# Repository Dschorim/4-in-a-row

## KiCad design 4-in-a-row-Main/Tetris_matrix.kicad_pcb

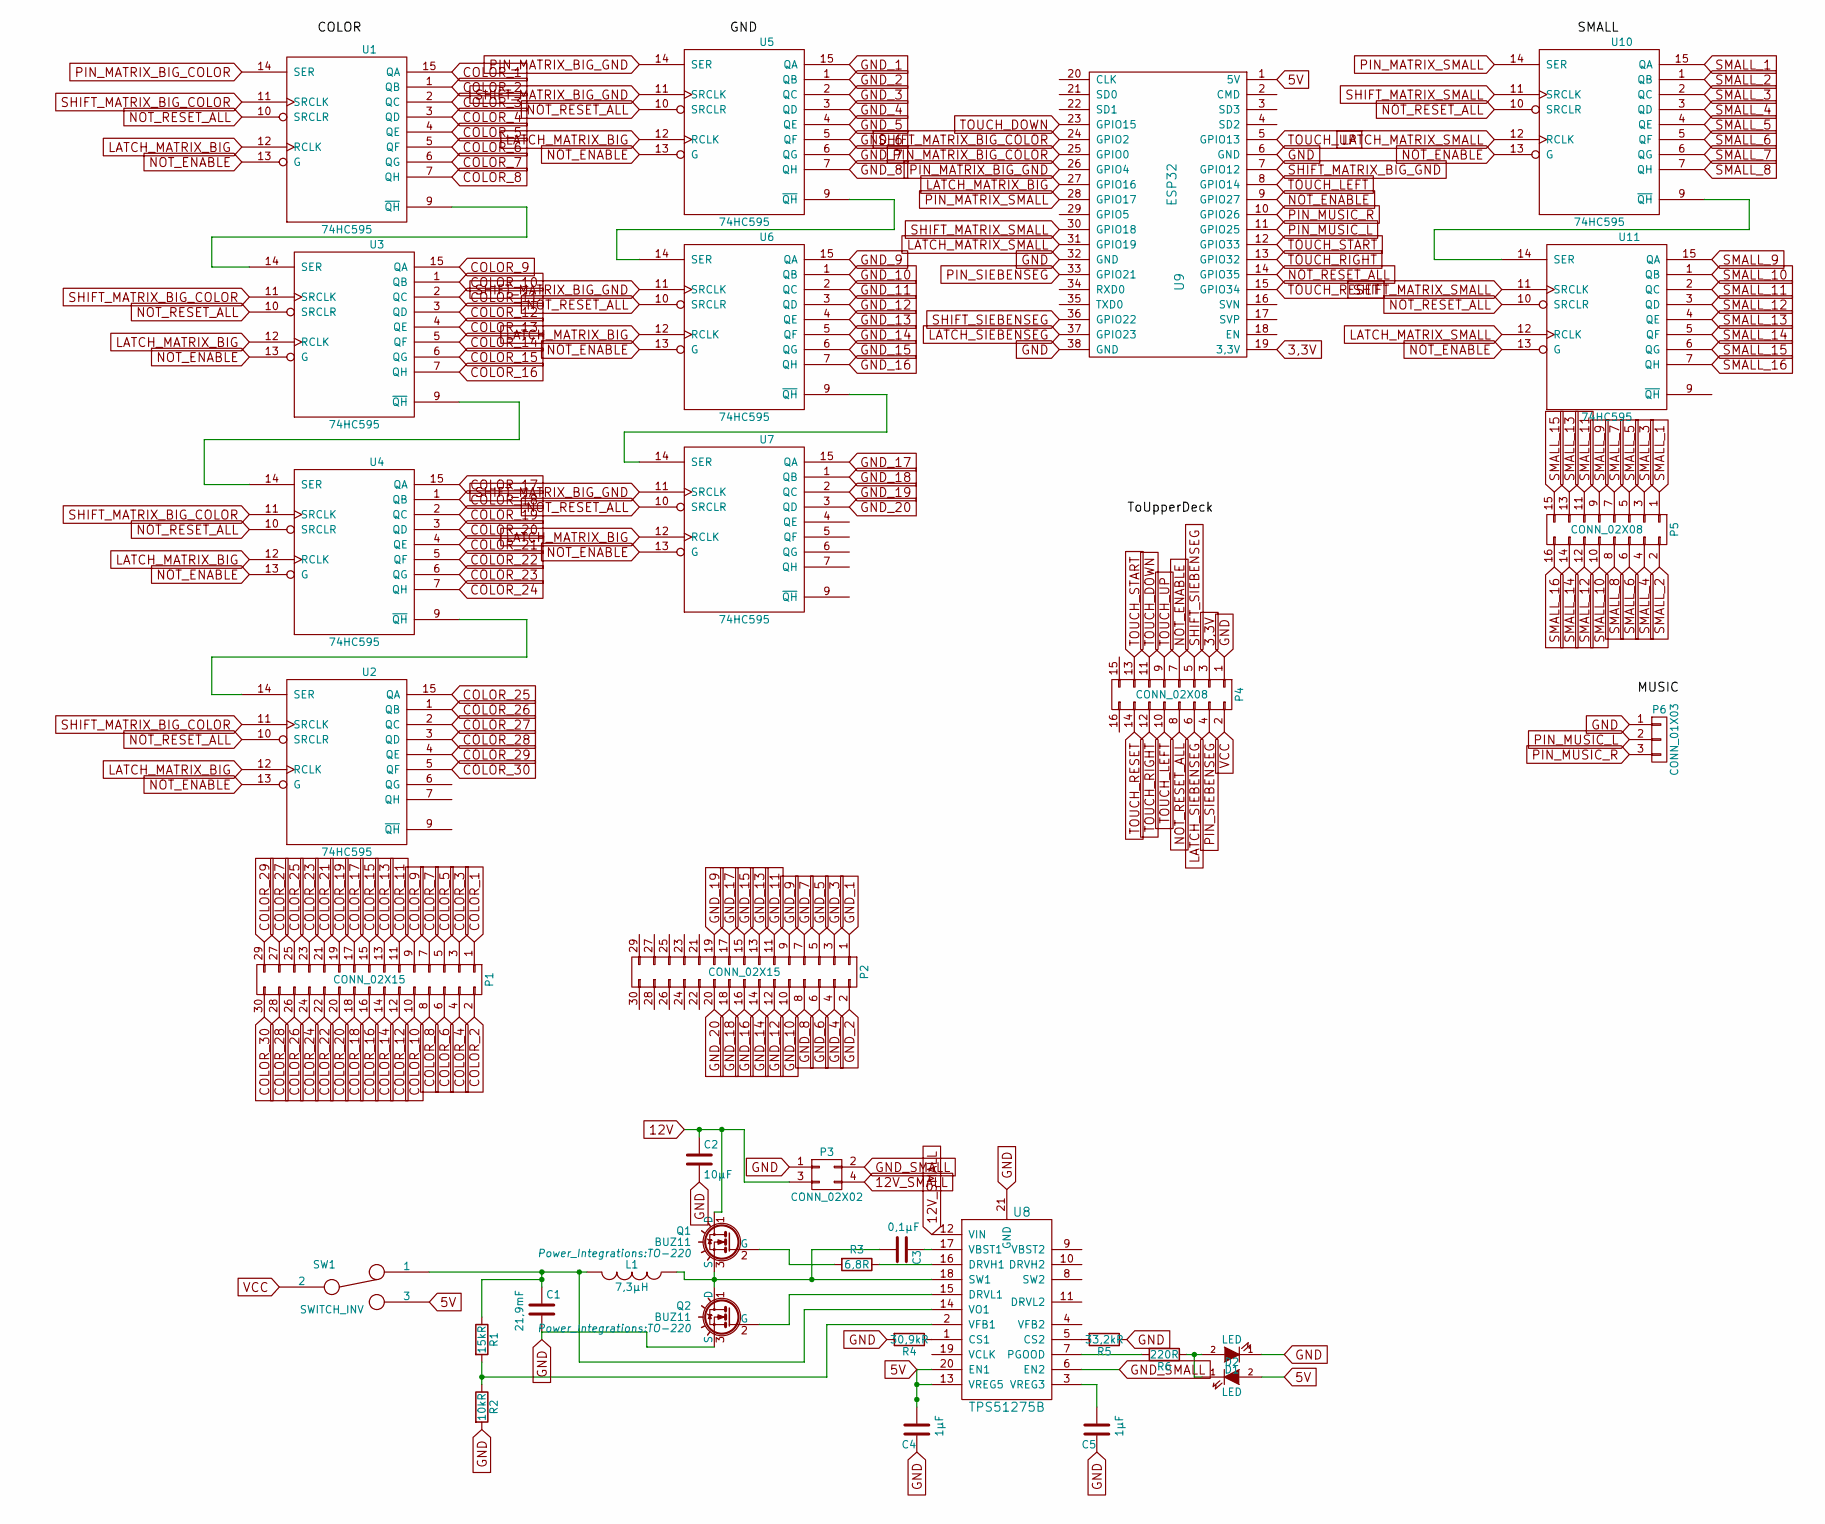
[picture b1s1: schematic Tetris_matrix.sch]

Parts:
C1: 21,9mF; C_0603_HandSoldering
C2: 10µF; C_0603_HandSoldering
C3: 0,1µF; C_0603_HandSoldering
C4, C5: 1µF; C_0603_HandSoldering
D1, D2: LED; LED_0603
L1: 7,3µH; SMDRI127
P1, P2: CONN_02X15; Pin_Header_Straight_2x15
P3: CONN_02X02; Pin_Header_Straight_2x02
P4, P5: CONN_02X08; Pin_Header_Straight_2x08
P6: CONN_01X03; Pin_Header_Straight_1x03
Q1, Q2: BUZ11; TO-220
R1: 15kR; R_0603_HandSoldering
R2: 10kR; R_0603_HandSoldering
R3: 6,8R; R_0603_HandSoldering
R4: 30,9kR; R_0603_HandSoldering
R5: 33,2kR; R_0603_HandSoldering
R6: 220R; R_0603_HandSoldering
SW1: SWITCH_INV; SW_Micro_SPST
U1, U2, U3, U4, U5, U6, U7, U10, U11: 74HC595; DIP-16_W7.62mm
U8: TPS51275B; UQFN-20-1EP_3x3mm_Pitch0.4mm
U9: ESP32; ESP32-9Pin

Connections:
3,3V: P4.3, U9.19 (3,3V)
5V: C4.2, D2.2 (A), SW1.3, U8.13 (VREG5), U8.20 (EN1), U9.1 (5V)
12V: C2.1, P3.3, Q1.1 (D)
12V_SMALL: P3.4, U8.12 (VIN)
COLOR_1: P1.1, U1.15 (QA)
COLOR_2: P1.2, U1.1 (QB)
COLOR_3: P1.3, U1.2 (QC)
COLOR_4: P1.4, U1.3 (QD)
COLOR_5: P1.5, U1.4 (QE)
COLOR_6: P1.6, U1.5 (QF)
COLOR_7: P1.7, U1.6 (QG)
COLOR_8: P1.8, U1.7 (QH)
COLOR_9: P1.9, U3.15 (QA)
COLOR_10: P1.10, U3.1 (QB)
COLOR_11: P1.11, U3.2 (QC)
COLOR_12: P1.12, U3.3 (QD)
COLOR_13: P1.13, U3.4 (QE)
COLOR_14: P1.14, U3.5 (QF)
COLOR_15: P1.15, U3.6 (QG)
COLOR_16: P1.16, U3.7 (QH)
COLOR_17: P1.17, U4.15 (QA)
COLOR_18: P1.18, U4.1 (QB)
COLOR_19: P1.19, U4.2 (QC)
COLOR_20: P1.20, U4.3 (QD)
COLOR_21: P1.21, U4.4 (QE)
COLOR_22: P1.22, U4.5 (QF)
COLOR_23: P1.23, U4.6 (QG)
COLOR_24: P1.24, U4.7 (QH)
COLOR_25: P1.25, U2.15 (QA)
COLOR_26: P1.26, U2.1 (QB)
COLOR_27: P1.27, U2.2 (QC)
COLOR_28: P1.28, U2.3 (QD)
COLOR_29: P1.29, U2.4 (QE)
COLOR_30: P1.30, U2.5 (QF)
GND: C1.2, C2.2, C4.1, C5.1, D1.1 (K), P3.1, P4.1, P6.1, Q2.3 (S), R2.2, R4.2, R5.1, U1.8 (GND), U2.8 (GND), U3.8 (GND), U4.8 (GND), U5.8 (GND), U6.8 (GND), U7.8 (GND), U8.21 (GND), U9.6 (GND), U9.32 (GND), U9.38 (GND), U10.8 (GND), U11.8 (GND)
GND_1: P2.1, U5.15 (QA)
GND_2: P2.2, U5.1 (QB)
GND_3: P2.3, U5.2 (QC)
GND_4: P2.4, U5.3 (QD)
GND_5: P2.5, U5.4 (QE)
GND_6: P2.6, U5.5 (QF)
GND_7: P2.7, U5.6 (QG)
GND_8: P2.8, U5.7 (QH)
GND_9: P2.9, U6.15 (QA)
GND_10: P2.10, U6.1 (QB)
GND_11: P2.11, U6.2 (QC)
GND_12: P2.12, U6.3 (QD)
GND_13: P2.13, U6.4 (QE)
GND_14: P2.14, U6.5 (QF)
GND_15: P2.15, U6.6 (QG)
GND_16: P2.16, U6.7 (QH)
GND_17: P2.17, U7.15 (QA)
GND_18: P2.18, U7.1 (QB)
GND_19: P2.19, U7.2 (QC)
GND_20: P2.20, U7.3 (QD)
GND_SMALL: P3.2, U8.6 (EN2)
LATCH_MATRIX_BIG: U1.12 (RCLK), U2.12 (RCLK), U3.12 (RCLK), U4.12 (RCLK), U5.12 (RCLK), U6.12 (RCLK), U7.12 (RCLK), U9.27 (GPIO16)
LATCH_MATRIX_SMALL: U9.31 (GPIO19), U10.12 (RCLK), U11.12 (RCLK)
LATCH_SIEBENSEG: P4.6, U9.37 (GPIO23)
NOT_ENABLE: P4.7, U1.13 (G), U2.13 (G), U3.13 (G), U4.13 (G), U5.13 (G), U6.13 (G), U7.13 (G), U9.9 (GPIO27), U10.13 (G), U11.13 (G)
NOT_RESET_ALL: P4.8, U1.10 (SRCLR), U2.10 (SRCLR), U3.10 (SRCLR), U4.10 (SRCLR), U5.10 (SRCLR), U6.10 (SRCLR), U7.10 (SRCLR), U9.14 (GPIO35), U10.10 (SRCLR), U11.10 (SRCLR)
unnamed: C1.1, L1.2, R1.1, SW1.1, U8.14 (VO1)
unnamed: C3.1, U8.17 (VBST1)
unnamed: C3.2, L1.1, Q1.3 (S), Q2.1 (D), U8.18 (SW1)
unnamed: C5.2, U8.3 (VREG3)
unnamed: D1.2 (A), D2.1 (K), R6.1
unnamed: Q1.2 (G), R3.2
unnamed: Q2.2 (G), U8.15 (DRVL1)
unnamed: R1.2, R2.1, U8.2 (VFB1)
unnamed: R3.1, U8.16 (DRVH1)
unnamed: R4.1, U8.1 (CS1)
unnamed: R5.2, U8.5 (CS2)
unnamed: R6.2, U8.7 (PGOOD)
unnamed: U1.9 (~QH), U3.14 (SER)
unnamed: U2.14 (SER), U4.9 (~QH)
unnamed: U3.9 (~QH), U4.14 (SER)
unnamed: U5.9 (~QH), U6.14 (SER)
unnamed: U6.9 (~QH), U7.14 (SER)
unnamed: U10.9 (~QH), U11.14 (SER)
PIN_MATRIX_BIG_COLOR: U1.14 (SER), U9.25 (GPIO0)
PIN_MATRIX_BIG_GND: U5.14 (SER), U9.26 (GPIO4)
PIN_MATRIX_SMALL: U9.28 (GPIO17), U10.14 (SER)
PIN_MUSIC_L: P6.2, U9.11 (GPIO25)
PIN_MUSIC_R: P6.3, U9.10 (GPIO26)
PIN_SIEBENSEG: P4.4, U9.33 (GPIO21)
SHIFT_MATRIX_BIG_COLOR: U1.11 (SRCLK), U2.11 (SRCLK), U3.11 (SRCLK), U4.11 (SRCLK), U9.24 (GPIO2)
SHIFT_MATRIX_BIG_GND: U5.11 (SRCLK), U6.11 (SRCLK), U7.11 (SRCLK), U9.7 (GPIO12)
SHIFT_MATRIX_SMALL: U9.30 (GPIO18), U10.11 (SRCLK), U11.11 (SRCLK)
SHIFT_SIEBENSEG: P4.5, U9.36 (GPIO22)
SMALL_1: P5.1, U10.15 (QA)
SMALL_2: P5.2, U10.1 (QB)
SMALL_3: P5.3, U10.2 (QC)
SMALL_4: P5.4, U10.3 (QD)
SMALL_5: P5.5, U10.4 (QE)
SMALL_6: P5.6, U10.5 (QF)
SMALL_7: P5.7, U10.6 (QG)
SMALL_8: P5.8, U10.7 (QH)
SMALL_9: P5.9, U11.15 (QA)
SMALL_10: P5.10, U11.1 (QB)
SMALL_11: P5.11, U11.2 (QC)
SMALL_12: P5.12, U11.3 (QD)
SMALL_13: P5.13, U11.4 (QE)
SMALL_14: P5.14, U11.5 (QF)
SMALL_15: P5.15, U11.6 (QG)
SMALL_16: P5.16, U11.7 (QH)
TOUCH_DOWN: P4.11, U9.23 (GPIO15)
TOUCH_LEFT: P4.10, U9.8 (GPIO14)
TOUCH_RESET: P4.14, U9.15 (GPIO34)
TOUCH_RIGHT: P4.12, U9.13 (GPIO32)
TOUCH_START: P4.13, U9.12 (GPIO33)
TOUCH_UP: P4.9, U9.5 (GPIO13)
VCC: P4.2, SW1.2, U1.16 (VCC), U2.16 (VCC), U3.16 (VCC), U4.16 (VCC), U5.16 (VCC), U6.16 (VCC), U7.16 (VCC), U10.16 (VCC), U11.16 (VCC)

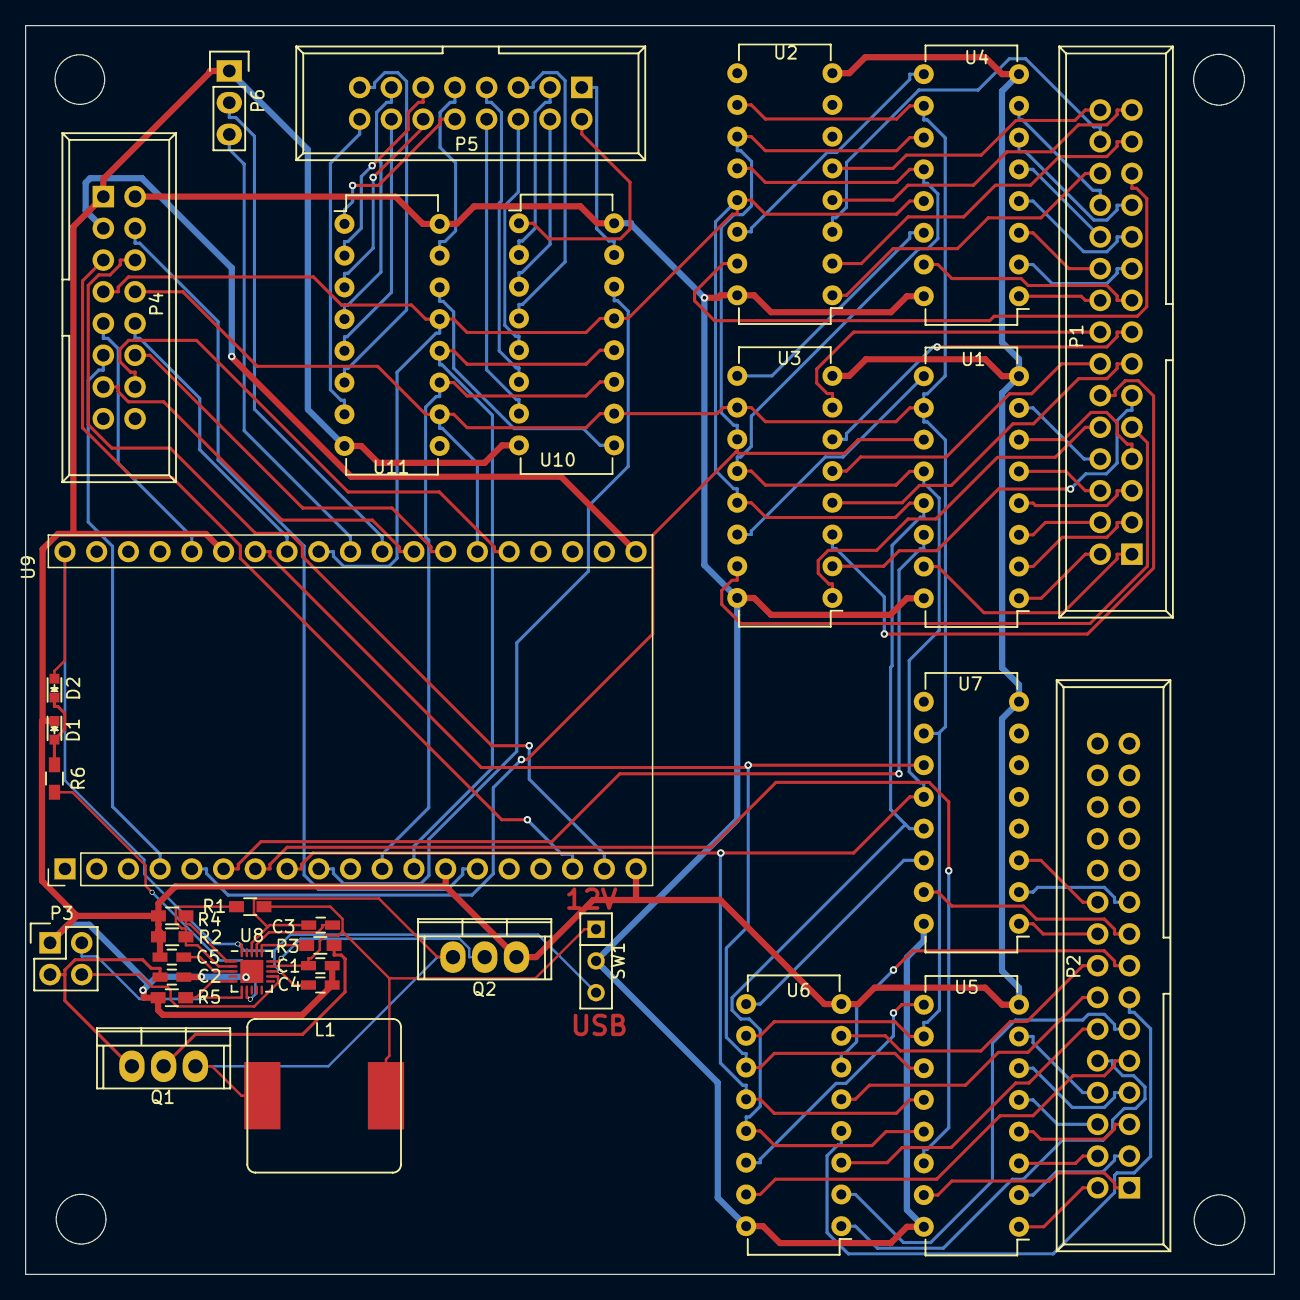
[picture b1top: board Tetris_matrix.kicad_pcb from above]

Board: 2 copper layers, 100.0 x 100.0 mm, 34 parts (0 on the bottom side), 112 nets.

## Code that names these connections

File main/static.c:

#define PIN_MATRIX_BIG_COLOR 0
#define SHIFT_MATRIX_BIG_COLOR 2
#define PIN_MATRIX_BIG_GND 4
#define SHIFT_MATRIX_BIG_GND 12
#define LATCH_MATRIX_BIG 16
#define PIN_MATRIX_SMALL 17
#define SHIFT_MATRIX_SMALL 18
#define LATCH_MATRIX_SMALL 19
#define PIN_SIEBENSEG 21
#define SHIFT_SIEBENSEG 22
#define LATCH_SIEBENSEG 23
#define NOT_ENABLE 27
//#define NOT_RESET_ALL 35 //pulled to 3,3V
#define PIN_MUSIC_L 25
#define PIN_MUSIC_R 26
#define TOUCH_UP 13
#define TOUCH_LEFT 14
#define TOUCH_DOWN 15
#define TOUCH_RIGHT 32
#define TOUCH_START 33
#define TOUCH_RESET 34

#define STANDARD_DELAY_TIME_MS 1000

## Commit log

2018-06-15 Added 7-Segment-Display support
2018-06-15 added eclipse file
2018-06-15 added binary files
2018-06-15 added project description
2018-06-15 updated Docs
2018-06-15 menuconfig update
2018-06-16 fixed dual channel audio
2018-06-16 fixed diagonal win recognition
2018-06-18 fixed time measurement
